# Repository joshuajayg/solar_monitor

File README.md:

# Solar Monitor

This is a solar power production and use monitoring system based on the LTC4151 IC by Analog.  Data is read by an ESP8266, sent over wifi using MQTT to a Raspberry Pi, stored in a database, then uploaded to a hosted webserver for display.  What you do with the data is up to you but the inclded firmware publishes MQTT messages to an MQTT server running on a separate computer in your local network.

You can see the system in work at http://yeolecabin.com/solar_complete.php

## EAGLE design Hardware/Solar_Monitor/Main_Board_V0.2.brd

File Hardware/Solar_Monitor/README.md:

The board uses six LTC4151-2 ICs, an ESP8266 running NODEMCU and one DROK buck converter.

The wires run from the board to the current shunts needs to be twisted pair wires.  This cuts down on EMI by common mode rejection.  For short runs, CAT5 wire works fine.

When adding a external input to D3, there is a voltage divider used to drop the voltage to 3.3V at the MCU.  You need to calculate these values as follows:
Vout = (Vin * R3) / (R4 + R3)

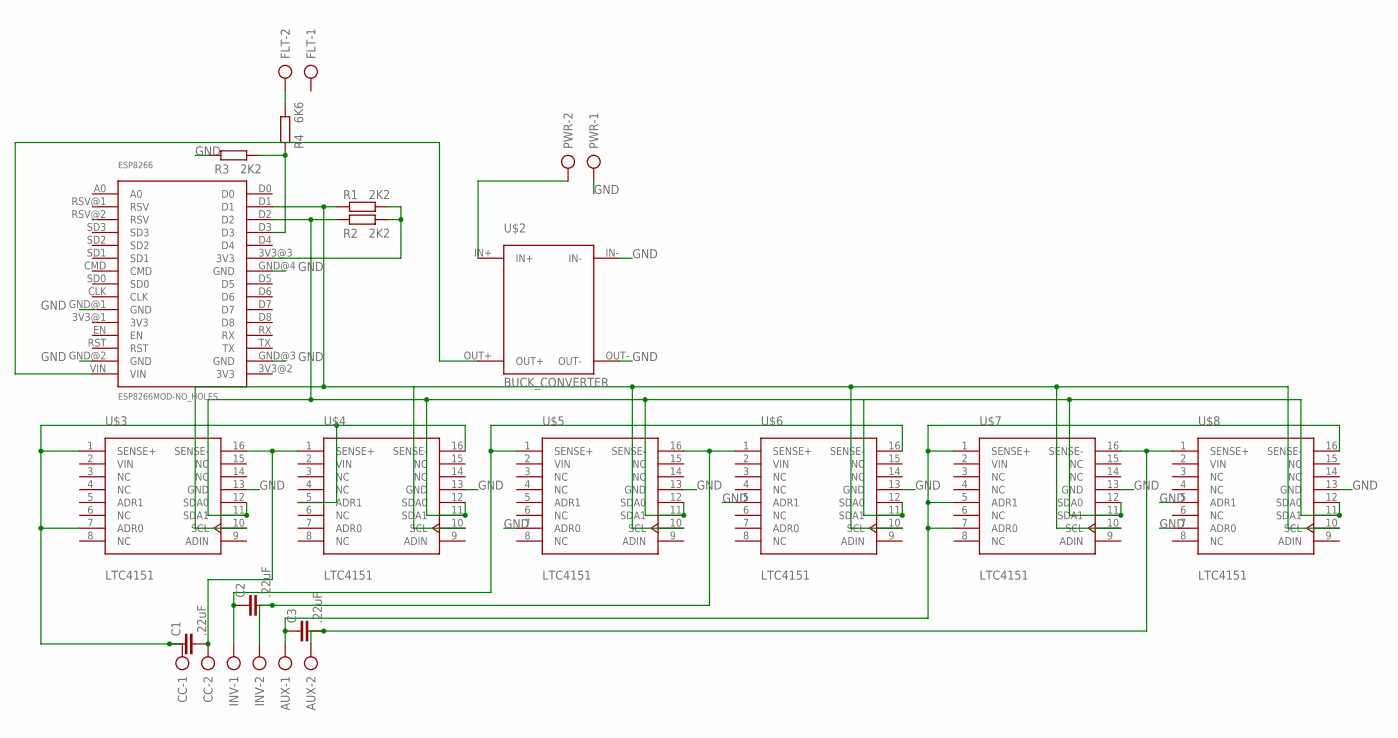
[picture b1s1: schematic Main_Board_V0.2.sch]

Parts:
AUX: AK500/2
C1, C2, C3: .22uF; C050-024X044
CC: AK500/2
ESP8266: ESP8266MOD-NO_HOLES
FLT: AK500/2
INV: AK500/2
PWR: AK500/2
R1, R2, R3: 2K2; 0207/10
R4: 6K6; 0207/10
U$2: BUCK_CONVERTER
U$3, U$4, U$5, U$6, U$7, U$8: LTC4151; SO16

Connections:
GND: ESP8266.GND@1 (GND), ESP8266.GND@2 (GND), ESP8266.GND@3 (GND), ESP8266.GND@4 (GND), PWR.1, R3.1, U$2.IN-, U$2.OUT-, U$3.13 (GND), U$4.13 (GND), U$5.7 (ADR0), U$5.13 (GND), U$6.5 (ADR1), U$6.13 (GND), U$7.13 (GND), U$8.5 (ADR1), U$8.7 (ADR0), U$8.13 (GND)
unnamed: FLT.2, R4.2
unnamed: ESP8266.D3, R3.2, R4.1
unnamed: ESP8266.VIN, U$2.OUT+
unnamed: C1.1, CC.1, U$3.1 (SENSE+), U$3.7 (ADR0), U$4.5 (ADR1), U$4.16 (SENSE-)
unnamed: C1.2, CC.2, U$3.16 (SENSE-), U$4.1 (SENSE+)
unnamed: C2.1, INV.1, U$5.1 (SENSE+), U$6.16 (SENSE-)
unnamed: C2.2, INV.2, U$5.16 (SENSE-), U$6.1 (SENSE+)
unnamed: AUX.1, C3.1, U$7.1 (SENSE+), U$7.5 (ADR1), U$7.7 (ADR0), U$8.16 (SENSE-)
unnamed: AUX.2, C3.2, U$7.16 (SENSE-), U$8.1 (SENSE+)
unnamed: ESP8266.D2, R2.1, U$3.11 (SDA1), U$3.12 (SDA0), U$4.11 (SDA1), U$4.12 (SDA0), U$5.11 (SDA1), U$5.12 (SDA0), U$6.11 (SDA1), U$6.12 (SDA0), U$7.11 (SDA1), U$7.12 (SDA0), U$8.11 (SDA1), U$8.12 (SDA0)
unnamed: ESP8266.3V3@3 (3V3), R1.2, R2.2
unnamed: ESP8266.D1, R1.1, U$3.10 (SCL), U$4.10 (SCL), U$5.10 (SCL), U$6.10 (SCL), U$7.10 (SCL), U$8.10 (SCL)
VIN: PWR.2, U$2.IN+, U$3.2 (VIN), U$4.2 (VIN), U$5.2 (VIN), U$6.2 (VIN), U$7.2 (VIN), U$8.2 (VIN)

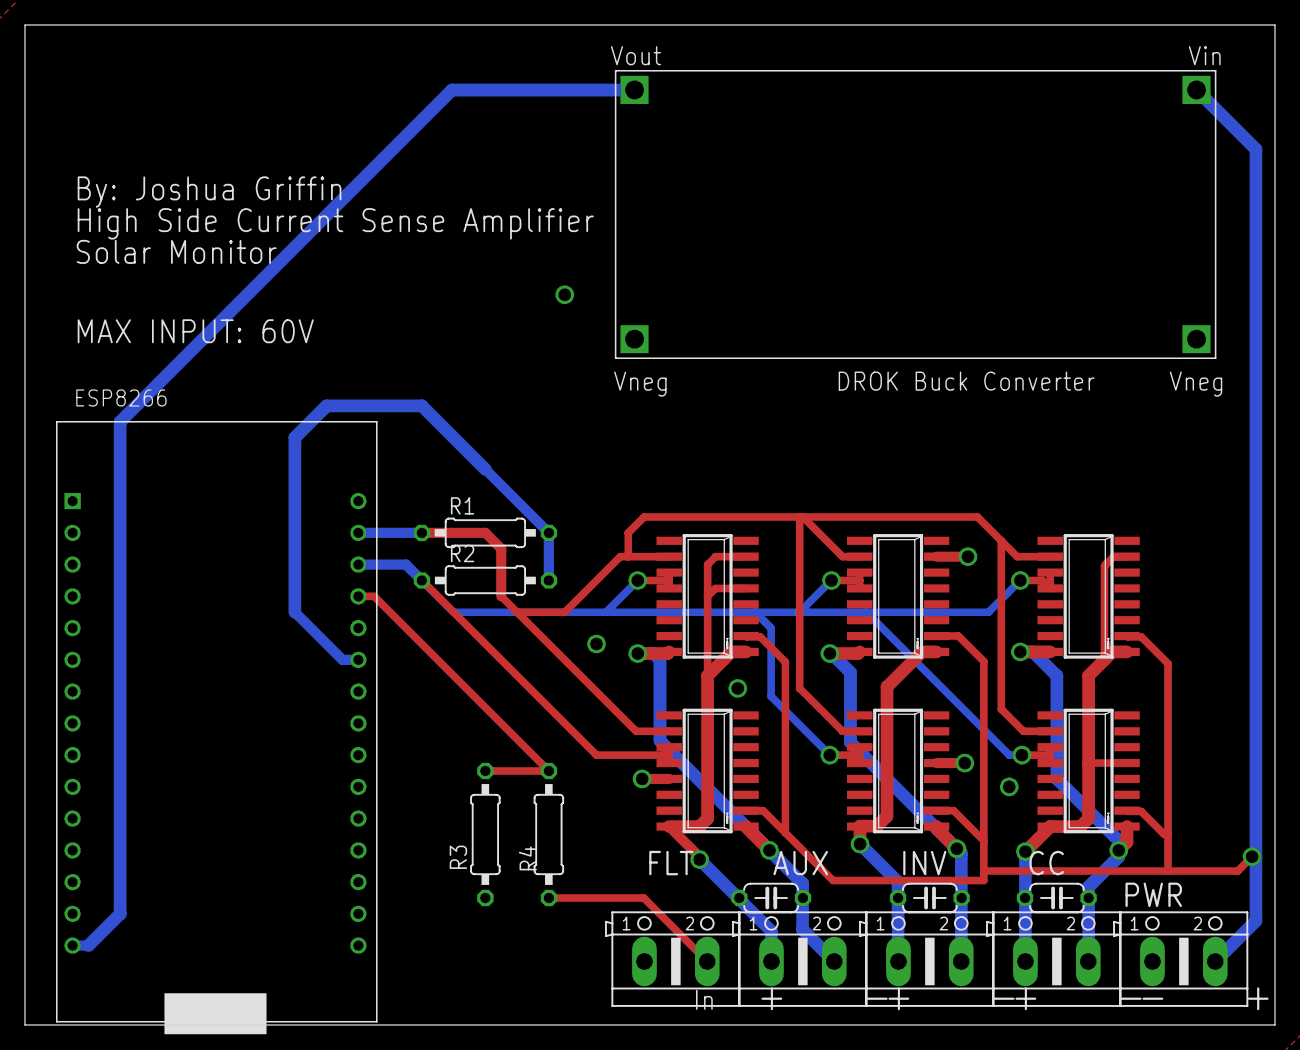
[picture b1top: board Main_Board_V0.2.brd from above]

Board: 2 copper layers, 100.0 x 80.0 mm, 20 parts (0 on the bottom side), 14 nets.

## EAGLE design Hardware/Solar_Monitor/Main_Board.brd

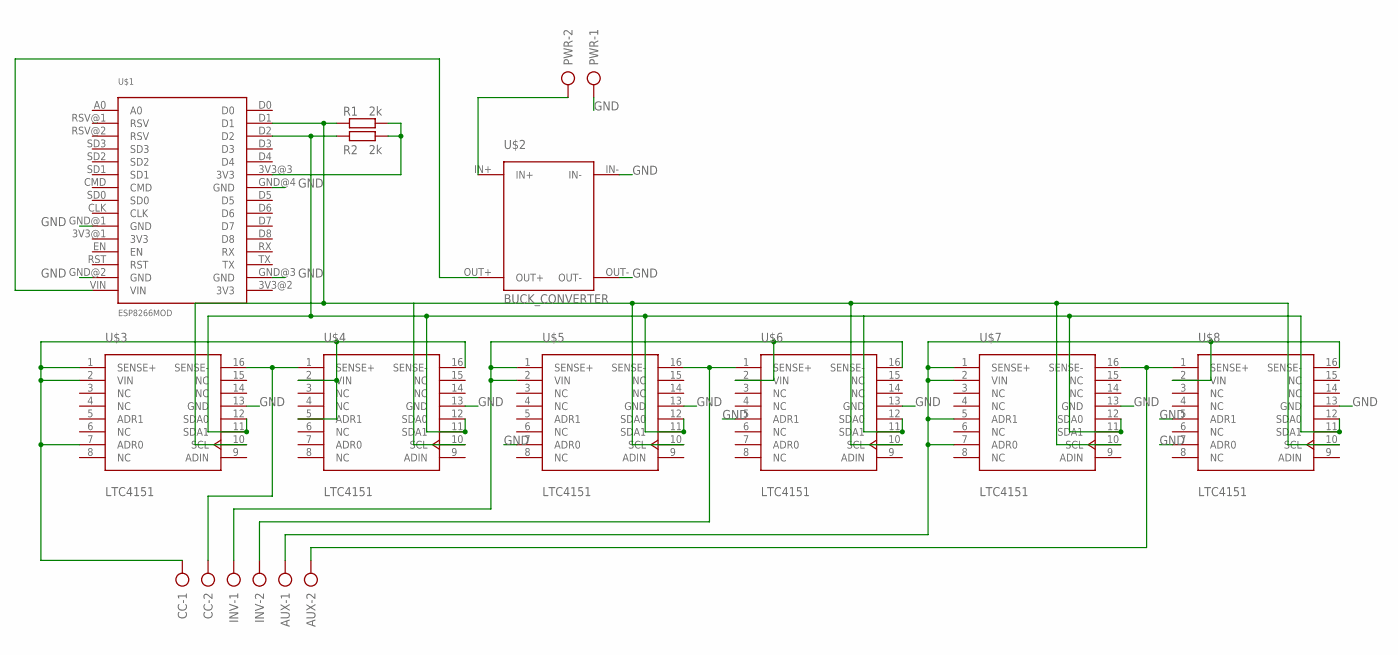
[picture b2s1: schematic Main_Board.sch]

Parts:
AUX: AK500/2
CC: AK500/2
INV: AK500/2
PWR: AK500/2
R1, R2: 2k; 0207/10
U$1: ESP8266MOD
U$2: BUCK_CONVERTER
U$3, U$4, U$5, U$6, U$7, U$8: LTC4151; SO16

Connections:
GND: PWR.1, U$1.GND@1 (GND), U$1.GND@2 (GND), U$1.GND@3 (GND), U$1.GND@4 (GND), U$2.IN-, U$2.OUT-, U$3.13 (GND), U$4.13 (GND), U$5.7 (ADR0), U$5.13 (GND), U$6.5 (ADR1), U$6.13 (GND), U$7.13 (GND), U$8.5 (ADR1), U$8.7 (ADR0), U$8.13 (GND)
unnamed: PWR.2, U$2.IN+
unnamed: U$1.VIN, U$2.OUT+
unnamed: CC.1, U$3.1 (SENSE+), U$3.2 (VIN), U$3.7 (ADR0), U$4.2 (VIN), U$4.5 (ADR1), U$4.16 (SENSE-)
unnamed: CC.2, U$3.16 (SENSE-), U$4.1 (SENSE+)
unnamed: INV.1, U$5.1 (SENSE+), U$5.2 (VIN), U$6.2 (VIN), U$6.16 (SENSE-)
unnamed: INV.2, U$5.16 (SENSE-), U$6.1 (SENSE+)
unnamed: AUX.1, U$7.1 (SENSE+), U$7.2 (VIN), U$7.5 (ADR1), U$7.7 (ADR0), U$8.2 (VIN), U$8.16 (SENSE-)
unnamed: AUX.2, U$7.16 (SENSE-), U$8.1 (SENSE+)
unnamed: R2.1, U$1.D2, U$3.11 (SDA1), U$3.12 (SDA0), U$4.11 (SDA1), U$4.12 (SDA0), U$5.11 (SDA1), U$5.12 (SDA0), U$6.11 (SDA1), U$6.12 (SDA0), U$7.11 (SDA1), U$7.12 (SDA0), U$8.11 (SDA1), U$8.12 (SDA0)
unnamed: R1.2, R2.2, U$1.3V3@3 (3V3)
unnamed: R1.1, U$1.D1, U$3.10 (SCL), U$4.10 (SCL), U$5.10 (SCL), U$6.10 (SCL), U$7.10 (SCL), U$8.10 (SCL)

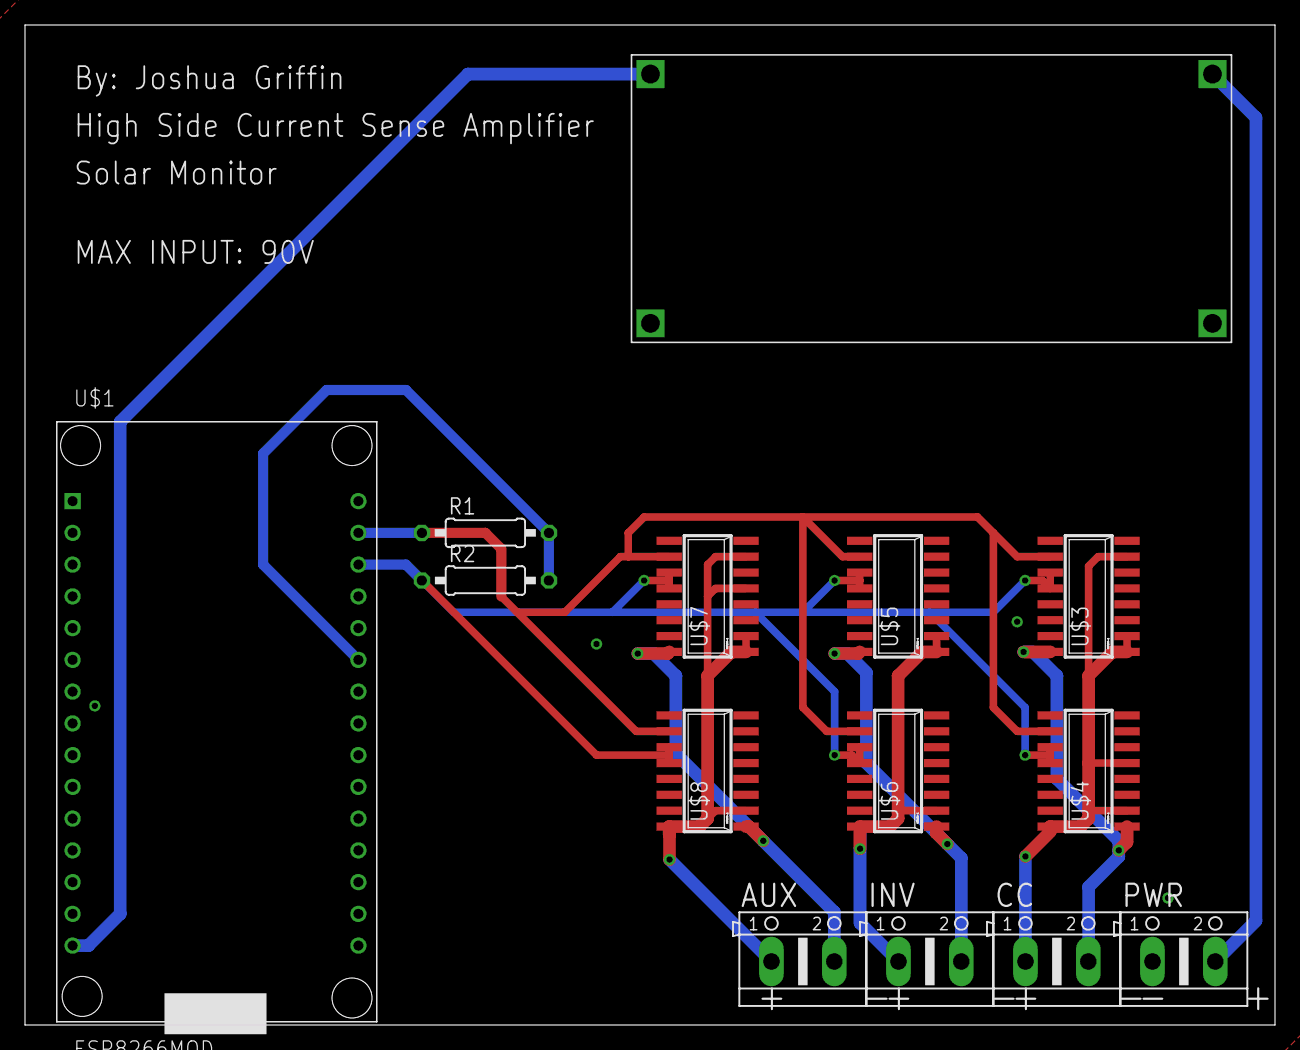
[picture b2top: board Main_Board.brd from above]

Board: 2 copper layers, 100.0 x 80.0 mm, 14 parts (0 on the bottom side), 12 nets.

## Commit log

2019-08-15 Update README.md
    Updated README
2019-08-15 Added Solar_Complete.ino
    Added Solar_Complete.ino to software and added README to explain some settings.
2019-08-15 Added Solar_Monitor board
    Added the first rendition of the solar monitor board schematic and PCB layout. Files are create in EAGLE.
2019-08-15 Update README.md
    Added website for example.
2019-08-16 Update README.md
    typo
2020-03-22 Uploaded V0.2 of board
    -Fixed IC power line source.
    -Fixed max voltage label
    -Added auxiliary input channel
2020-03-22 Added V0.2 of board
    -Fixed IC power one problem
    -Fixed mislabel of max voltage
    -Added aux input option
2020-03-22 Update README.md
    Added version used for sketch upload as I have seen some issues with new options in the past.
2020-03-22 Update Solar_Complete.ino
    -Removed ADIN readings
    -Added ability to read auxiliary input on pin D3
    -Added ability to set initial values of several parameters so it reads correctly on startup
2020-03-23 Update README.md
    Added voltage divider equation
2021-08-22 Adding PDF versions of the schematic and pcb
    For easier viewing for those without Eagle already installed
2026-06-04 added callbacks for setting live values through MQTT payload
2026-06-05 Revise README
